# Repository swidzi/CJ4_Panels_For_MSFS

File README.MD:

# CJ4 Panels

CJ4 Panels are designed to enable an avgeek to build their own Control Panels for [CJ4 Working Tilte Mod](https://github.com/Working-Title-MSFS-Mods/fspackages) for MS Flight Simulator 2020.
Those consist of:

* Eagle files for PCBs (orderable or to be made on a CNC-mill)
* List of electronic components
* STL files for 3d printing
* Inkscape SVG files for laser engraving
* Arduino firmware
* FSUIPC Configuration

Those additionally use certain components from [FlightSimMaker](https://www.thingiverse.com/flightsimmaker/designs) excelent G1000 project - namely [push button switches](https://www.thingiverse.com/thing:4019943) and [Dual Concentric Rotary Encoders](https://www.thingiverse.com/thing:4373531).

## Folder layout

Each panel and component has its own folder. Inside that folder you will find relevant files sorted by type - Eagle, STL etc.
If a certain component requires extra information it will have its own README.MD file.

## Available Panels:

### Primary Flight Display / Display Control Panel

Using a single Arduino/Sparkfun Pro Micro it presents itself to MSFS as a 26 button joystick.

 <span style="display:block;text-align:center"></span>

## Coming Soon:

### Autopilot / Flight Guindance Panel

Using a single Arduino/Sparkfun Pro Micro it presents itself to MSFS as a 29 button joystick.

 <span style="display:block;text-align:center"></span>

### Flight Management System (Computer) / Multi-Function Control and Display Unit

Using a single Arudino/Sparkfun Pro Micro and the MMJoy2 interface it presents itself as a 96+ button joystick.

 <span style="display:block;text-align:center"></span>

### Multi Function Display / Cursor Control Panel

 <span style="display:block;text-align:center"></span>

## Requirements

* MS Flight Simulator *(I tested it on Steam version)*
* FSUIPC v7 paid version - [link](https://secure.simmarket.com/john-dowson-fsuipc7-for-msfs.phtml)
* MobiFlight WASM module - [link](https://www.mobiflight.com/en/index.html)
* Arduino IDE v1.8.5 or higher - [link](https://www.arduino.cc/)
* Libraries:
	* [Common Bus Encoders](https://github.com/j-bellavance/CommonBusEncoders)
	* Joystick library - available via Manage Libraries in Arduino IDE
	* Adafruit MCP230177 library - available via Manage Libraries in Arduino IDE
* Arduino Pro Micro (based on Atmega32u4) *This is very important! Other AVR chips WILL **NOT** work*

## Building the physical part of the panels

### 3d Printing

Coming soon...

### Laser engraving

Coming soon...

### Making PCBs

Coming soon...

## Installation

#### Installing the software
1. If you have not done so, purchase and install FSUIPC v7
2. Download and install MobiFlight. You do not need to actually be running this software - you just need it's WASM module. Install it in accordance to MobiFlight instructions.
3. Download and install Arduino IDE
* Install required libraries
* If you are using the SparkFun Pro Micro or its clone - Install the proper AVR boards definitions to Arduino Board Manager \([tutorial](https://learn.sparkfun.com/tutorials/installing-arduino-ide/board-add-ons-with-arduino-board-manager)\)

#### Setting up the software:

FSUIPC:
* Copy files from FSUIPC_Configuration folder to your FSUIPC installation folder
* Edit FSUIPC.ini file and modify two lines:
```
[General]
UseProfiles=Files
```
AND
```
[Buttons]
PollInterval=10
```
It is possible that your Arduino Pro Micro joystick will register at a different letter. If that happens you can either:
* Edit the FSUIPC.ini file and change letter assignments in section \[JoyNames\], or
* Edit the Profile files and change letter assignments for each control: For example if you change from Joystick D to F you need to change every occurrence of **PD** to **PF**

#### MS Flight Simulator Setup

At current stage of simulator development no setup is necessary. It is all handled by FSUIPC & MobiFlight combination.

## Usage

Just use like would any joystick controller!

## Contributing

If you find a bug or have a question, feel free to message me on github or to open an Issue.

## Acknowledgments

Many thanks to wonderful people at FlightSimMaker group discord server as well as to all authors who have provided libraries and freeware software available for flightsimmers worldwide

## Questions / Contact

Just drop me an email at swidzi@gmail.com

### License
[GNU GPLv3](https://choosealicense.com/licenses/gpl-3.0/)

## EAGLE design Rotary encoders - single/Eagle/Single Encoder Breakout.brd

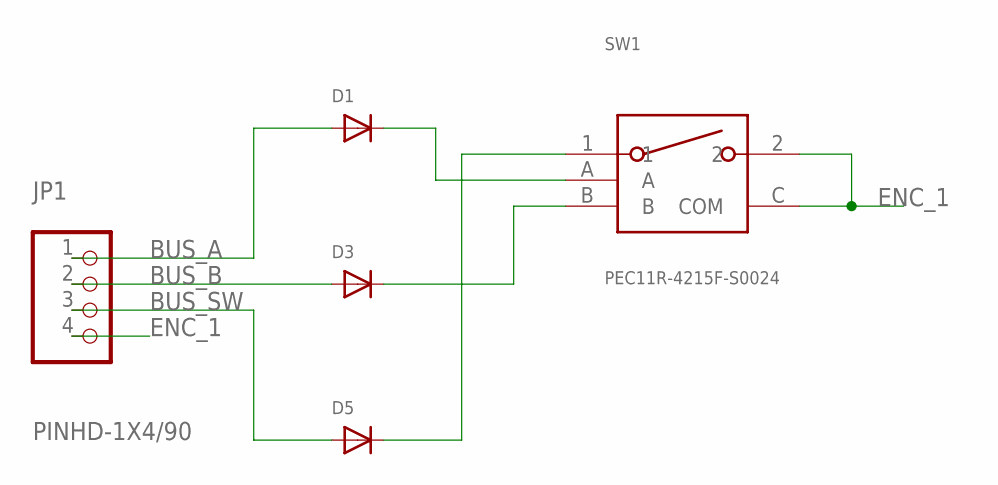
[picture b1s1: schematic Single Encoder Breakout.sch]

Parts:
D1, D3, D5: DIODESOD-123; SOD-123
JP1: PINHD-1X4/90; 1X04/90
SW1: PEC11R-4215F-S0024

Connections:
BUS_A: D1.A, JP1.1
BUS_B: D3.A, JP1.2
BUS_SW: D5.A, JP1.3
ENC_1: JP1.4, SW1.2, SW1.C (COM)
unnamed: D1.C, SW1.A
unnamed: D3.C, SW1.B
unnamed: D5.C, SW1.1

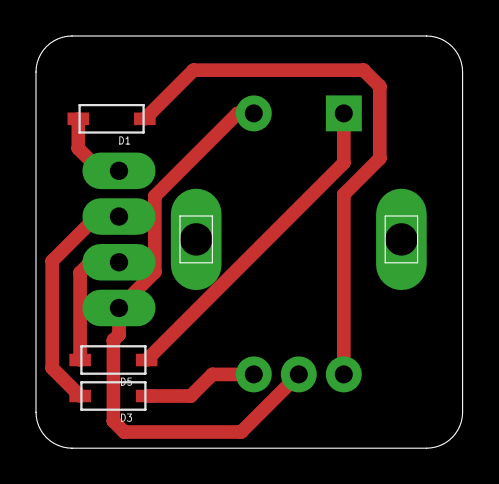
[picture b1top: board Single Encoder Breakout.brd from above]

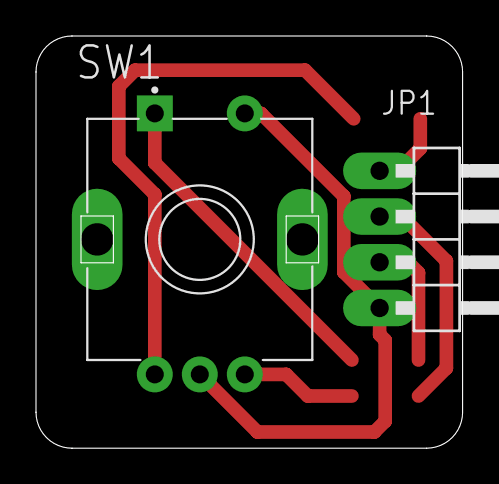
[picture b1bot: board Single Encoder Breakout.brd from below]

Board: 2 copper layers, 23.7 x 22.9 mm, 5 parts (2 on the bottom side), 7 nets.

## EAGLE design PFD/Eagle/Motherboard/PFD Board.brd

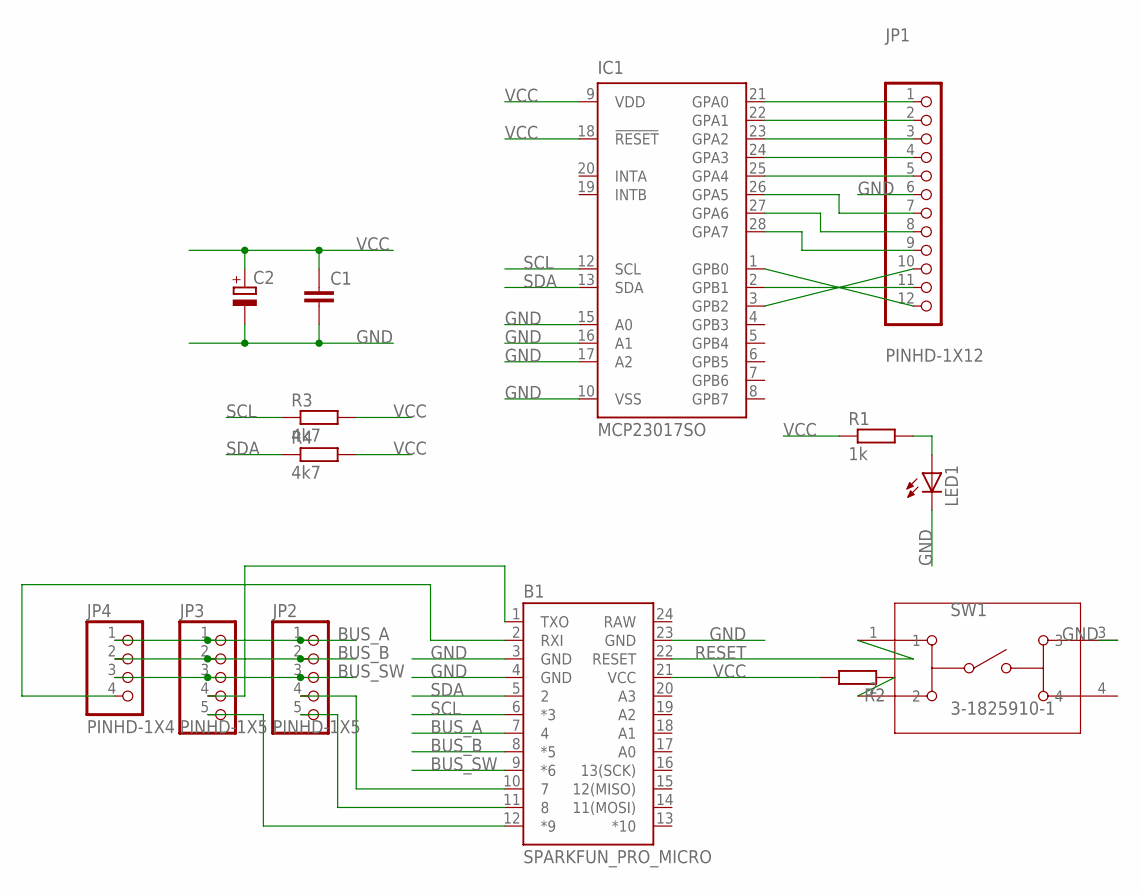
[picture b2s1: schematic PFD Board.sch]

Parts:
B1: SPARKFUN_PRO_MICRO
C1: C-EU025-025X050; C025-025X050
C2: CPOL-EUE2.5-5; E2,5-5
IC1: MCP23017SO; SO28W
JP1: PINHD-1X12; 1X12
JP2, JP3: PINHD-1X5; 1X05
JP4: PINHD-1X4; 1X04
LED1: LED3MM
R1: 1k; 0207/10
R2: R-EU_0207/10; 0207/10
R3, R4: 4k7; 0207/10
SW1: 3-1825910-1; SW4_1825910-H

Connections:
BUS_A: B1.7 (4), JP2.1, JP3.1, JP4.1
BUS_B: B1.8 (*5), JP2.2, JP3.2, JP4.2
BUS_SW: B1.9 (*6), JP2.3, JP3.3, JP4.3
GND: B1.3 (GND), B1.4 (GND), B1.23 (GND), C1.2, C2.-, IC1.10 (VSS), IC1.15 (A0), IC1.16 (A1), IC1.17 (A2), JP1.6, LED1.K (C), SW1.3
unnamed: B1.10 (7), JP2.4
unnamed: B1.11 (8), JP2.5
unnamed: B1.12 (*9), JP3.5
unnamed: B1.2 (RXI), JP4.4
unnamed: B1.1 (TXO), JP3.4
unnamed: IC1.21 (GPA0), JP1.1
unnamed: IC1.22 (GPA1), JP1.2
unnamed: IC1.23 (GPA2), JP1.3
unnamed: IC1.24 (GPA3), JP1.4
unnamed: IC1.25 (GPA4), JP1.5
unnamed: IC1.1 (GPB0), JP1.12
unnamed: IC1.26 (GPA5), JP1.7
unnamed: IC1.27 (GPA6), JP1.8
unnamed: IC1.28 (GPA7), JP1.9
unnamed: IC1.3 (GPB2), JP1.10
unnamed: IC1.2 (GPB1), JP1.11
unnamed: LED1.A, R1.2
unnamed: R2.1, SW1.2
RAW: B1.24 (RAW)
RESET: B1.22 (RESET), SW1.1
SCL: B1.6 (*3), IC1.12 (SCL), R3.1
SDA: B1.5 (2), IC1.13 (SDA), R4.1
VCC: B1.21 (VCC), C1.1, C2.+, IC1.9 (VDD), IC1.18 (!RESET), R1.1, R2.2, R3.2, R4.2

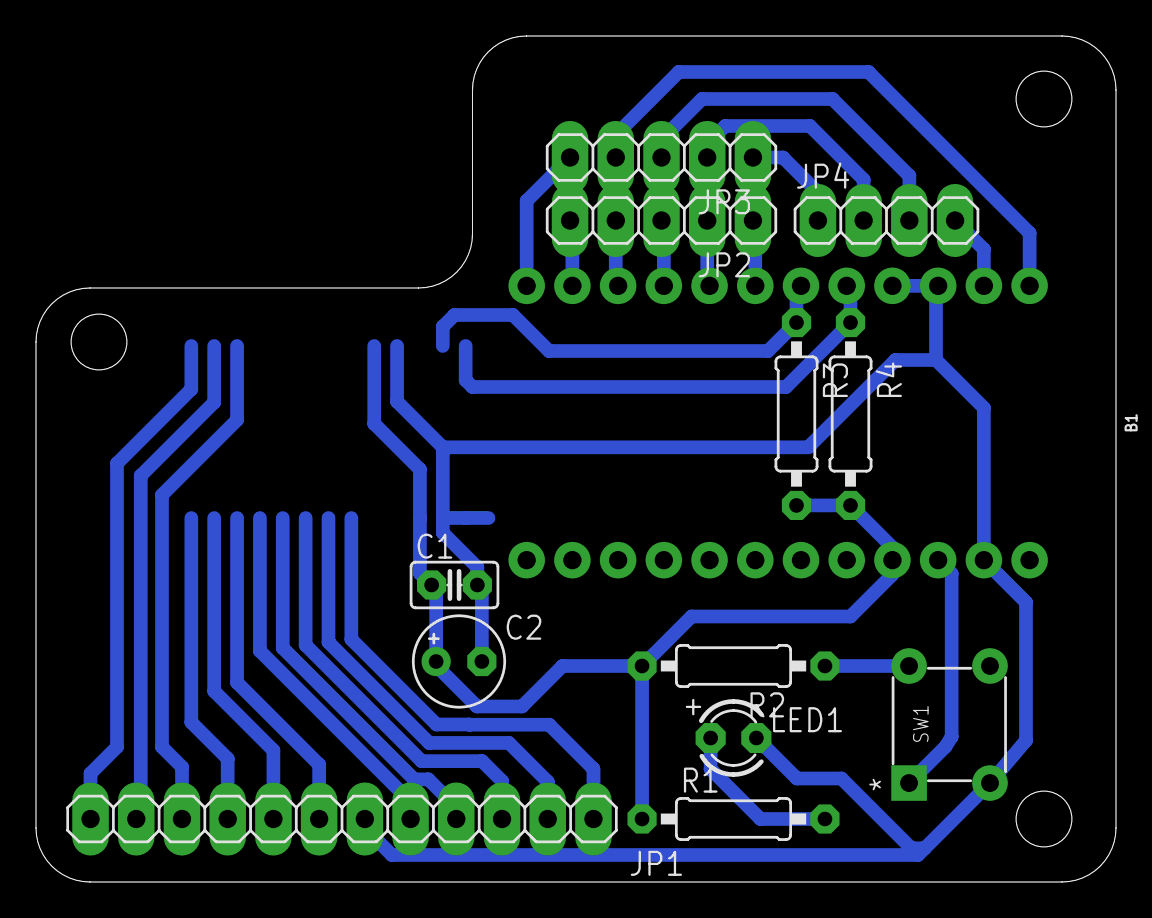
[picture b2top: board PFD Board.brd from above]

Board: 2 copper layers, 60.0 x 47.0 mm, 14 parts (1 on the bottom side), 26 nets.

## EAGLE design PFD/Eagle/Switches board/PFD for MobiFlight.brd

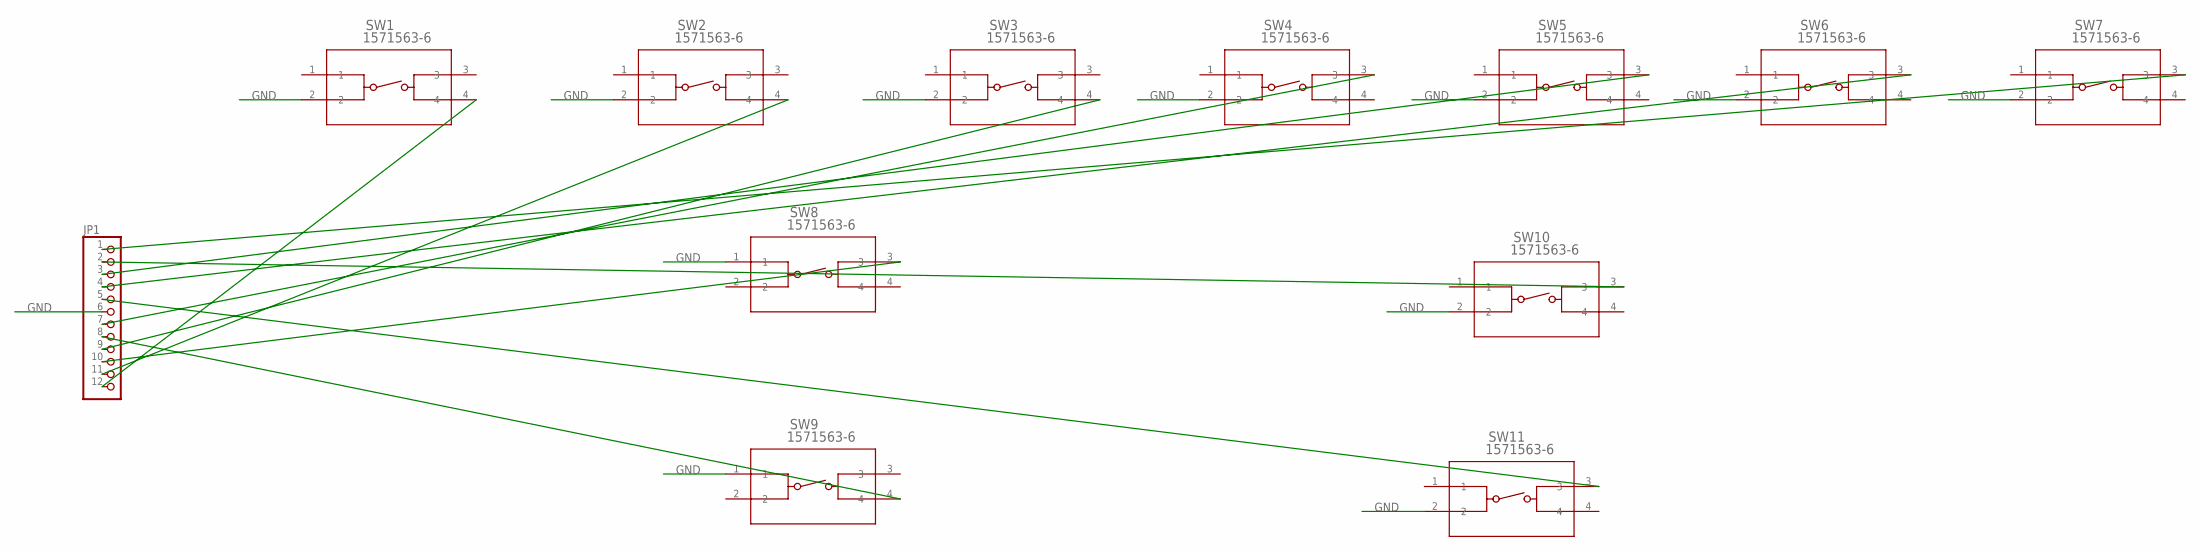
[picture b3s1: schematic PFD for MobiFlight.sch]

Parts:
JP1: PINHD-1X12; 1X12
SW1, SW2, SW3, SW4, SW5, SW6, SW7, SW8, SW9, SW10, SW11: 1571563-6; SW4_1437565-E

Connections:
GND: JP1.6, SW1.2, SW2.2, SW3.2, SW4.2, SW5.2, SW6.2, SW7.2, SW8.1, SW9.1, SW10.2, SW11.2
unnamed: JP1.7, SW4.3
unnamed: JP1.9, SW3.4
unnamed: JP1.8, SW9.4
unnamed: JP1.10, SW8.3
unnamed: JP1.11, SW2.4
unnamed: JP1.12, SW1.4
unnamed: JP1.3, SW5.3
unnamed: JP1.5, SW11.3
unnamed: JP1.4, SW6.3
unnamed: JP1.1, SW7.3
unnamed: JP1.2, SW10.3

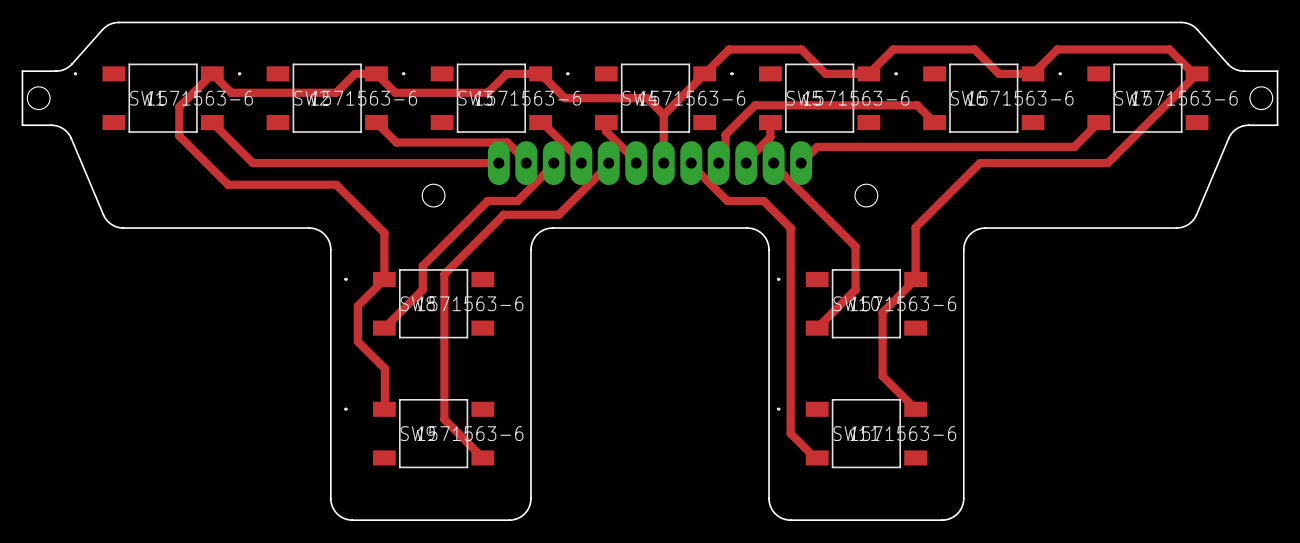
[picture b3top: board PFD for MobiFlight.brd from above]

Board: 2 copper layers, 116.0 x 46.0 mm, 12 parts (1 on the bottom side), 12 nets.

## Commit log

2021-03-28 PFD/DCP Initial release
2021-03-28 Create LICENSE
2021-03-29 Code clean-up (comments).
2021-03-29 Corrected RESET switch design.
2021-03-29 Modified README.MD
2021-03-29 Initial release - Rotary breakout boards

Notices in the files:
parts and their libraries:
SparkFun-Boards: Licensing: Creative Commons ShareAlike 4.0 International - https://creativecommons.org/licenses/by-sa/4.0
COPYRIGHT: Copyright (C) 2016 Accelerated Designs. All rights reserved
